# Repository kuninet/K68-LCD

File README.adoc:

= LCD SC1603 BOARD for MC68系マイコン 

== 概要
* 16桁x2行のLCDモジュール SC1602をMC68系マイコン(SBC6303とか)へ接続するボードです。

== 説明
* MC68系マイコン(SBC6303とか)へ接続するボードです。
* 74HC138でドレスデコードします。

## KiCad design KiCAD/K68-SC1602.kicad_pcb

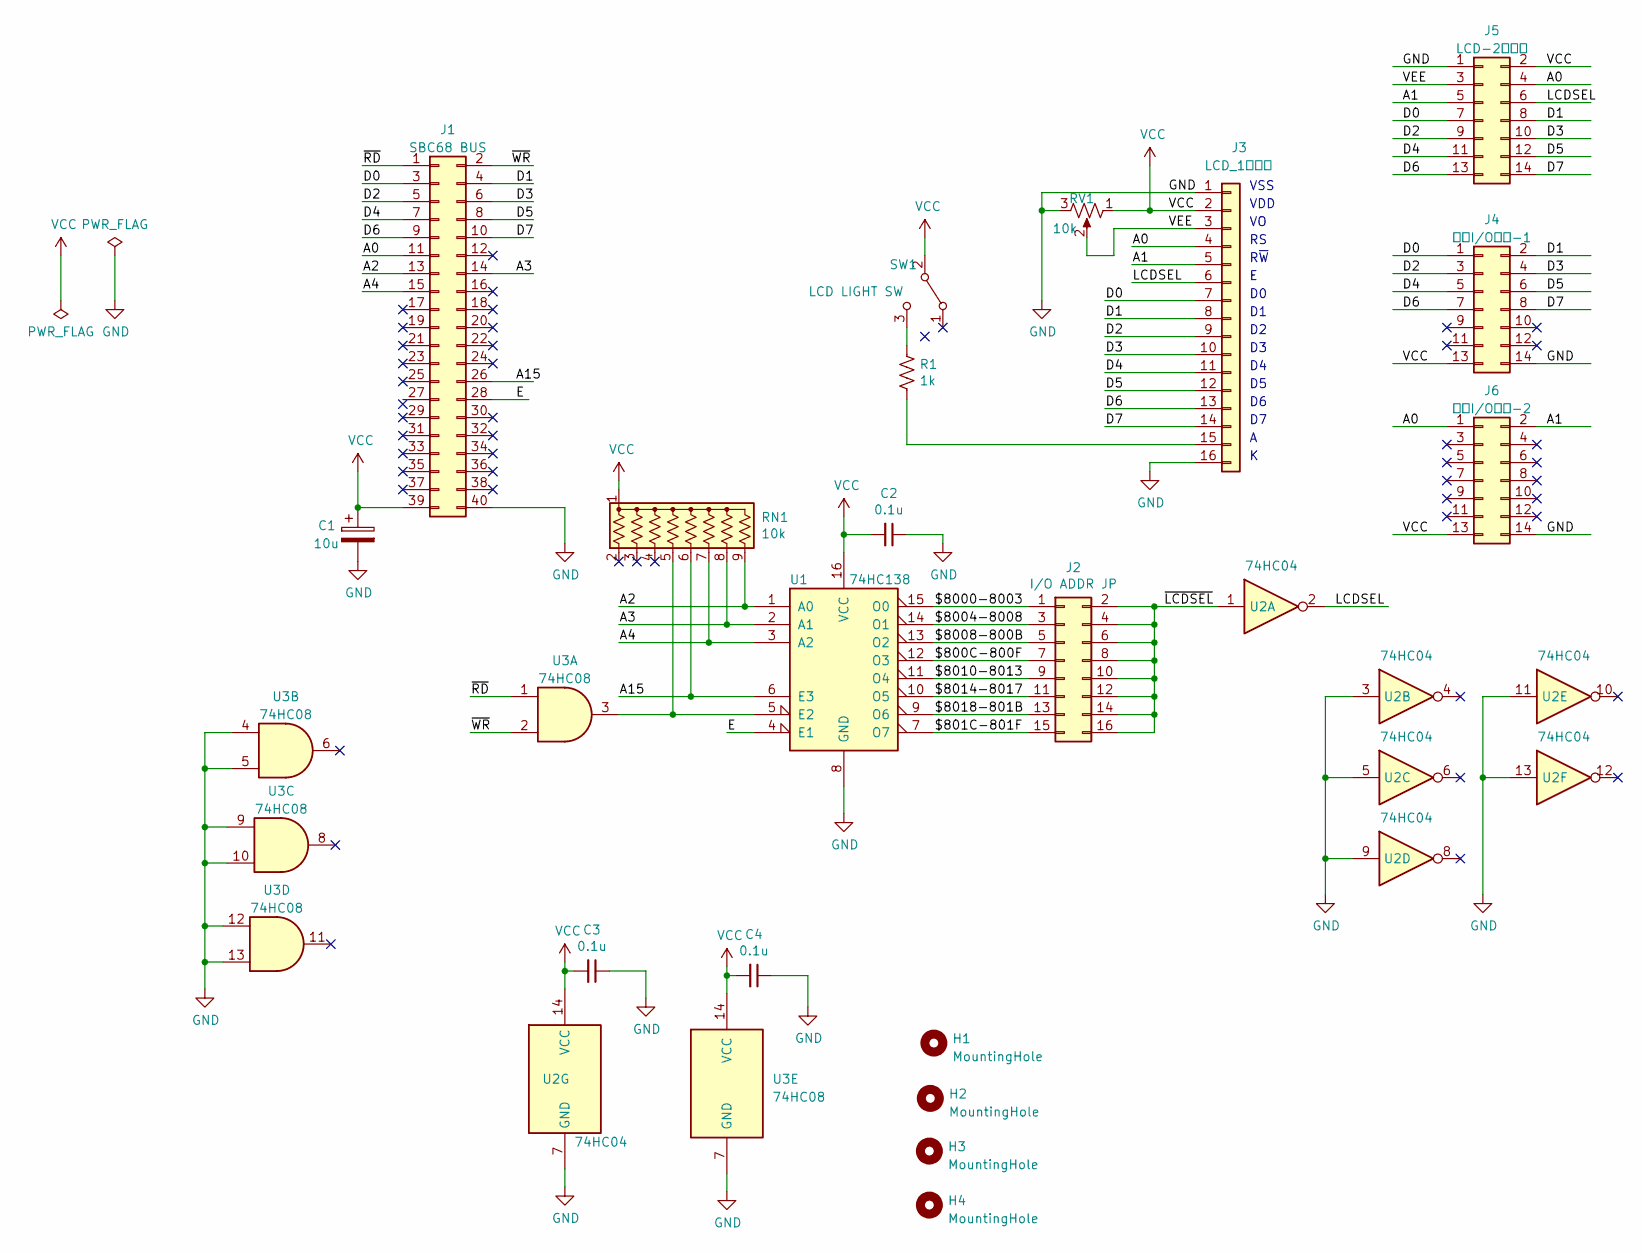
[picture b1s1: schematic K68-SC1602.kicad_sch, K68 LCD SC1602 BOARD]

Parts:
C1: 10u; CP_Radial_D5.0mm_P2.50mm
C2, C3, C4: 0.1u; C_Disc_D3.0mm_W1.6mm_P2.50mm
H1, H2, H3, H4: MountingHole; MountingHole_3.2mm_M3
J1: SBC68 BUS; PinHeader_2x20_P2.54mm_Horizontal
J2: I/O ADDR JP; PinHeader_2x08_P2.54mm_Vertical
J3: LCD_1列端子; PinHeader_1x16_P2.54mm_Vertical
J4: 外部I/O端子-1; PinHeader_2x07_P2.54mm_Vertical
J5: LCD-2列端子; PinHeader_2x07_P2.54mm_Vertical
J6: 外部I/O端子-2; PinHeader_2x07_P2.54mm_Vertical
R1: 1k; R_Axial_DIN0207_L6.3mm_D2.5mm_P10.16mm_Horizontal
RN1: 10k; R_Array_SIP9
RV1: 10k; Potentiometer_Vishay_T73YP_Vertical
SW1: LCD LIGHT SW; PinHeader_1x03_P2.54mm_Vertical
U1: 74HC138; DIP-16_W7.62mm_Socket
U2: 74HC04; DIP-14_W7.62mm_Socket
U3: 74HC08; DIP-14_W7.62mm_Socket

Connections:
/$800C-800F: J2.7, U1.12 (O3)
/$801C-801F: J2.15, U1.7 (O7)
/$8000-8003: J2.1, U1.15 (O0)
/$8004-8008: J2.3, U1.14 (O1)
/$8008-800B: J2.5, U1.13 (O2)
/$8010-8013: J2.9, U1.11 (O4)
/$8014-8017: J2.11, U1.10 (O5)
/$8018-801B: J2.13, U1.9 (O6)
/A0: J1.11, J3.4, J5.4, J6.1
/A1: J3.5, J5.5, J6.2
/A2: J1.13, RN1.9 (R8), U1.1 (A0)
/A3: J1.14, RN1.8 (R7), U1.2 (A1)
/A4: J1.15, RN1.7 (R6), U1.3 (A2)
/A15: J1.26, RN1.6 (R5), U1.6 (E3)
/D0: J1.3, J3.7, J4.1, J5.7
/D1: J1.4, J3.8, J4.2, J5.8
/D2: J1.5, J3.9, J4.3, J5.9
/D3: J1.6, J3.10, J4.4, J5.10
/D4: J1.7, J3.11, J4.5, J5.11
/D5: J1.8, J3.12, J4.6, J5.12
/D6: J1.9, J3.13, J4.7, J5.13
/D7: J1.10, J3.14, J4.8, J5.14
/E: J1.28, U1.4 (E1)
/LCDSEL: J3.6, J5.6, U2.2
/VEE: J3.3, J5.3, RV1.2
/~LCDSEL: J2.2, J2.4, J2.6, J2.8, J2.10, J2.12, J2.14, J2.16, U2.1
/~RD: J1.1, U3.1
/~WR: J1.2, U3.2
GND: C1.2, C2.1, C3.1, C4.1, J1.40, J3.1, J3.16, J4.14, J5.1, J6.14, RV1.3, U1.8 (GND), U2.3, U2.5, U2.7 (GND), U2.9, U2.11, U2.13, U3.4, U3.5, U3.7 (GND), U3.9, U3.10, U3.12, U3.13
unnamed: J3.15, R1.2
unnamed: RN1.5 (R4), U1.5 (E2), U3.3
unnamed: R1.1, SW1.3 (C)
VCC: C1.1, C2.2, C3.2, C4.2, J1.39, J3.2, J4.13, J5.2, J6.13, RN1.1 (common), RV1.1, SW1.2 (B), U1.16 (VCC), U2.14 (VCC), U3.14 (VCC)

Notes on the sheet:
VSS
VDD
R~{W}

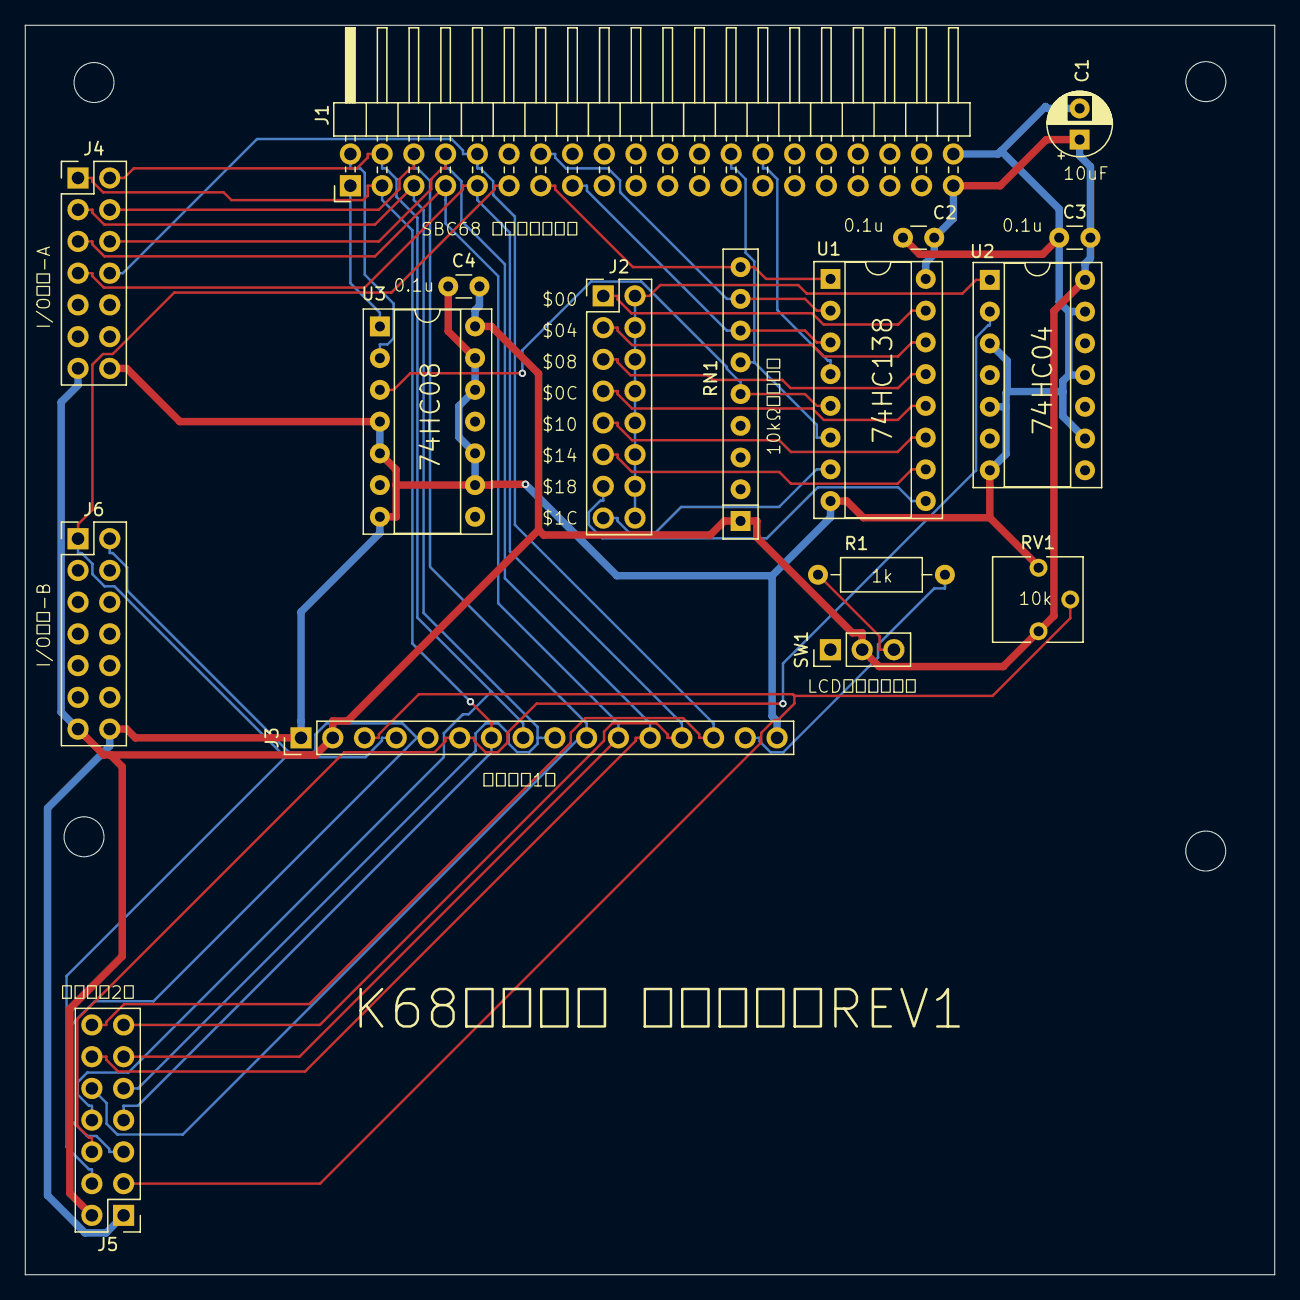
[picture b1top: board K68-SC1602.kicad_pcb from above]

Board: 2 copper layers, 100.0 x 100.0 mm, 21 parts (0 on the bottom side), 33 nets.

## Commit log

2023-03-24 REV1 基板データ ガーバー出力
